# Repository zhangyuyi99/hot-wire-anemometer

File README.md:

# Hot wire anemometer

This project includes the design and implementation of a Wi-Fi enabled anemometer. The anemometer consists of a hardware portion which includes the PCB designs for the main board and logic board and a software portion which includes the firmware for operating the anemometer. The anemometer uses a hot wire method for wind speed measurement, and it includes a function to monitor battery voltage, disabling wind readings when the voltage drops below 7V until it recovers.

## Contents
1. [Hardware](#Hardware)
2. [Software](#Software)
3. [Usage](#Usage)
4. [File Structure](#File-Structure)

## Hardware
The hardware part consists of two boards: 

### Main Board
The main board uses the analog hot wire anemometer method for wind measurement. It is powered and sends signal to the logic board.

### Logic Board
The logic board contains an ESP32 processor which receives signals from the main board. It sends the data either via a serial port or Wi-Fi. It also monitors the battery voltage and provides visual feedback using LEDs.

## Software
The software part consists of firmware written for the ESP32 processor. The firmware contains routines to read data from the main board, manage Wi-Fi connectivity, monitor battery voltage, and control LED indicators.

### Python Scripts
There are two Python scripts provided for reading data:

1. `read_from_esp32.py`: Reads data over Wi-Fi. To use this, the anemometer and the computer receiving data must be on the same Wi-Fi network.

2. `read_from_esp32_serial.py`: Reads data over a serial port.

## Usage

To use this anemometer, you will need to:

1. Print the main board and logic board based on the provided PCB design files.
2. Perform necessary wirings to power up the main board and send signals to the logic board.
3. Set up Wi-Fi connectivity in the firmware.
4. Compile and upload the firmware to the logic board.
5. Calibrate the anemometer. To calibrate, place the anemometer in an environment with the same ambient temperature as the actual measurement environment. Adjust the Through Hole Potentiometer on each anemometer until the no-wind reading reaches 1000-1200. Each anemometer is paired with a green LED on the logic board. The LED lights up when the no-wind reading is in the desired range.
6. Run the provided Python scripts to receive and save the wind data. Each wind data packet is a string of numbers separated by commas. The first number is a timestamp, and the rest are the anemometer readings.

## Modes

The anemometer supports four running modes:
* READ_ANEMOMETER
* SEND_PIN_READ
* PRINT_IP
* CALIBRATE

The default mode is CALIBRATE.

## File Structure

The files in this project are organized as follows:

- plot.pptx
- logic_board/
    - Various KiCAD and SVG files for logic board design
- main_board/
    - Various KiCAD and SVG files for main board design
- firmware/
    - anemometer/
        - Python scripts to read data from the anemometer
        - ESP32 firmware files
        - Additional files for Visual Studio Code and PlatformIO

For a detailed view of the file structure, refer to the file list provided earlier.

## Note

The readings of different anemometers for the same wind strength might not be the same. However, the change in readings should accurately reflect the changes in wind conditions.

## Contribution 

The design of main board and logic board is done by Filip Ayazi. The firmware is written by Yuyi Zhang and ChatGPT, actually mostly by ChatGPT.

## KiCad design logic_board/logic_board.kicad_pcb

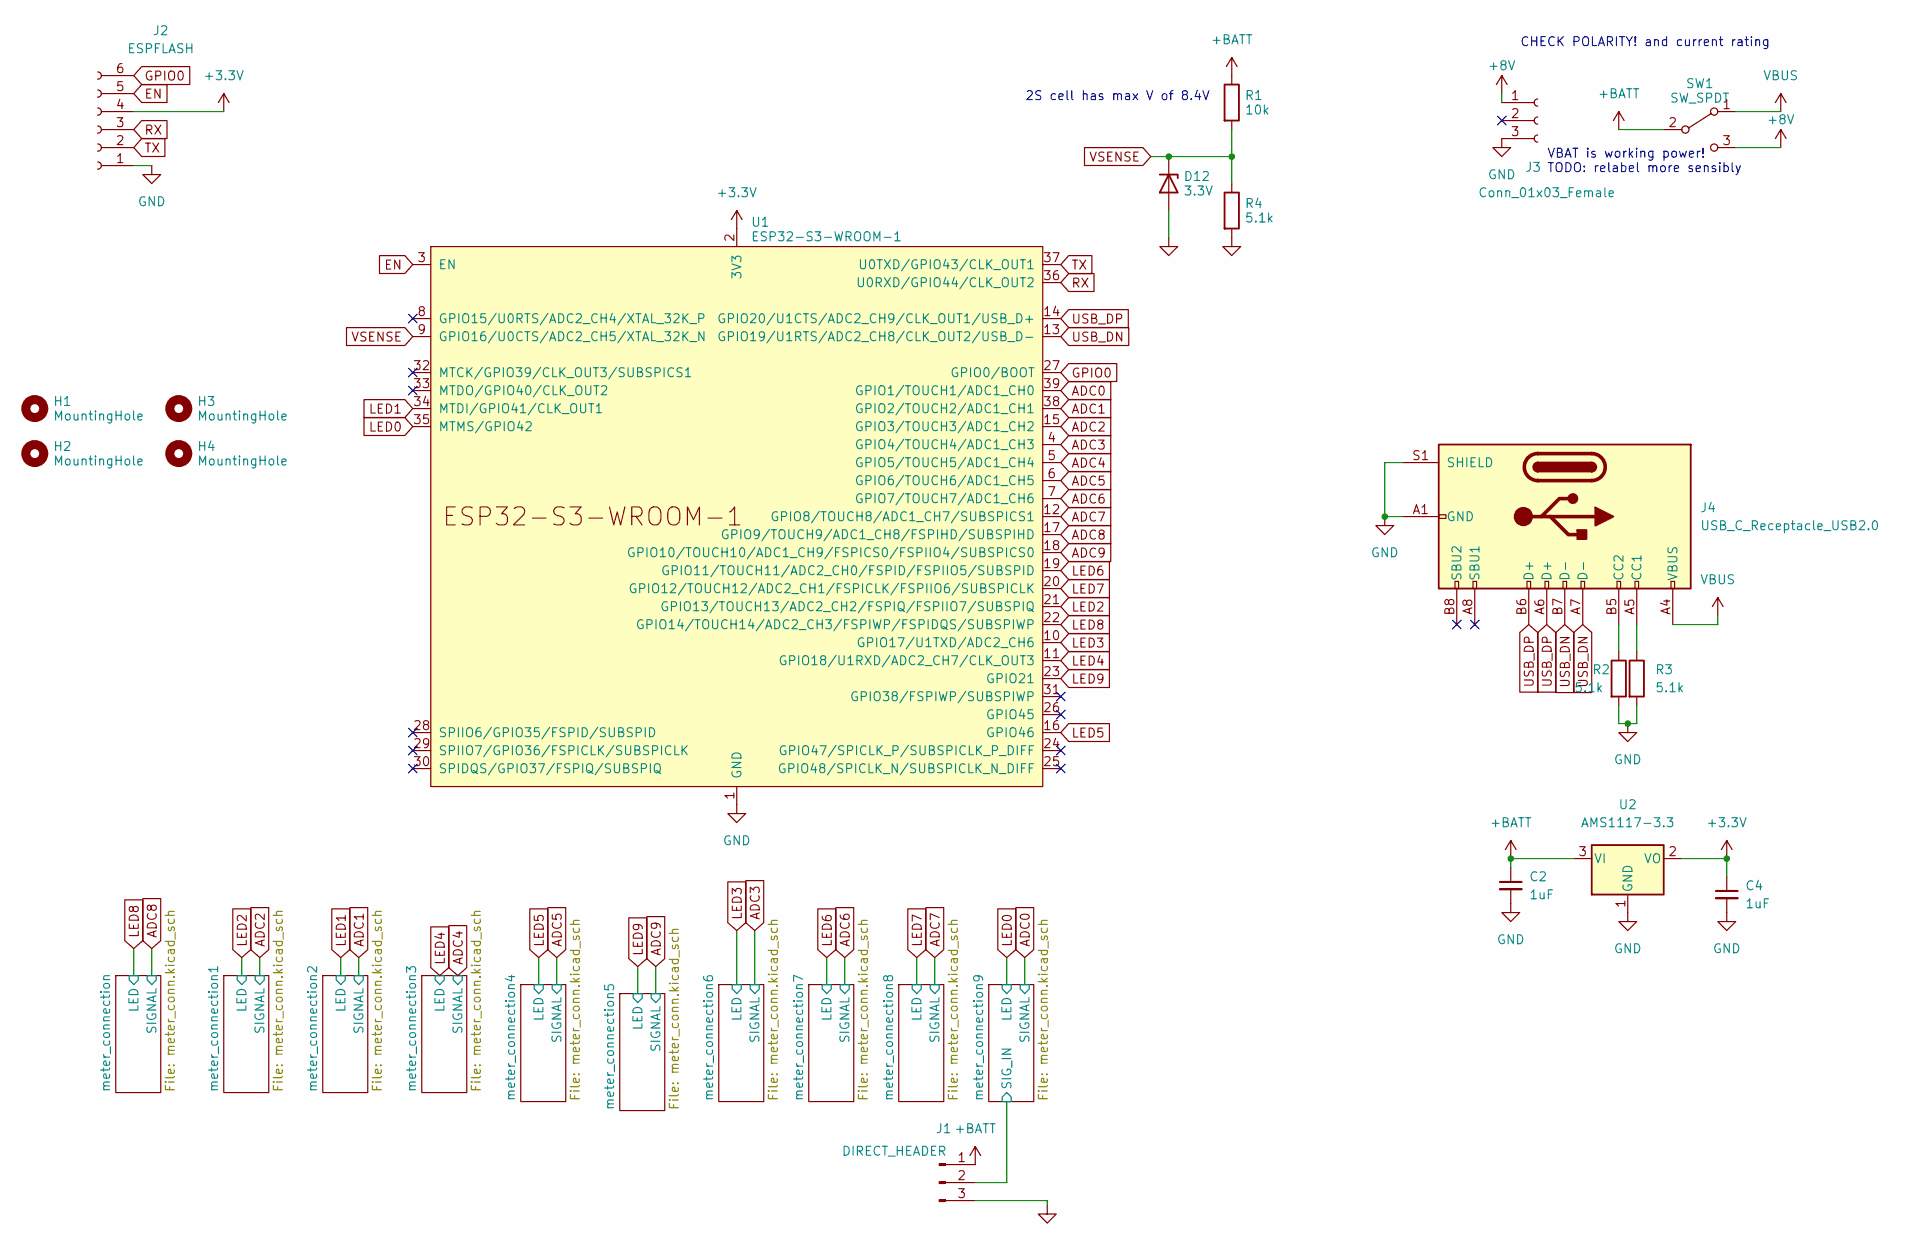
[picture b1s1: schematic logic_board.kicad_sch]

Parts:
C2, C4: 1uF; C_0402_1005Metric; JLC C83063
D12: 3.3V; D_SOD-523; JLC C2999960
H1, H2, H3, H4: MountingHole; MountingHole_3.2mm_M3
J1: DIRECT_HEADER; PinHeader_1x03_P2.54mm_Vertical; JLC C5116482
J2: ESPFLASH; PinSocket_1x06_P2.54mm_Vertical; JLC C5224026
J3: Conn_01x03_Female; JST_XH_B3B-XH-A_1x03_P2.50mm_Vertical; JLC C144394
J4: USB_C_Receptacle_USB2.0; USB_C_Receptacle_HRO_TYPE-C-31-M-12; JLC C2765186
R1: 10k; R_0402_1005Metric; JLC C407753
R2, R3, R4: 5.1k; R_0603_1608Metric; JLC C105580
SW1: SW_SPDT; switch_4.7mm; JLC C319012
U1: ESP32-S3-WROOM-1; JLC C2913197
U2: AMS1117-3.3; SOT-223-3_TabPin2; JLC C173386

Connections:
+3V3: C4.1, J2.4, U1.2 (3V3), U2.2 (VO)
+8V: J3.1, SW1.3 (C)
+BATT: C2.1, J1.1, R1.1, SW1.2 (B), U2.3 (VI); also elsewhere on the board
/meter_connection9/SIG_IN: J1.2; also elsewhere on the board
ADC0: U1.39 (GPIO1/TOUCH1/ADC1_CH0); also elsewhere on the board
ADC1: U1.38 (GPIO2/TOUCH2/ADC1_CH1); also elsewhere on the board
ADC2: U1.15 (GPIO3/TOUCH3/ADC1_CH2); also elsewhere on the board
ADC3: U1.4 (GPIO4/TOUCH4/ADC1_CH3); also elsewhere on the board
ADC4: U1.5 (GPIO5/TOUCH5/ADC1_CH4); also elsewhere on the board
ADC5: U1.6 (GPIO6/TOUCH6/ADC1_CH5); also elsewhere on the board
ADC6: U1.7 (GPIO7/TOUCH7/ADC1_CH6); also elsewhere on the board
ADC7: U1.12 (GPIO8/TOUCH8/ADC1_CH7/SUBSPICS1); also elsewhere on the board
ADC8: U1.17 (GPIO9/TOUCH9/ADC1_CH8/FSPIHD/SUBSPIHD); also elsewhere on the board
ADC9: U1.18 (GPIO10/TOUCH10/ADC1_CH9/FSPICS0/FSPIIO4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); also elsewhere on the board
EN: J2.5, U1.3 (EN)
GND: C2.2, C4.2, D12.2 (A), J1.3, J2.1, J3.3, J4.A1 (GND), J4.A12 (GND), J4.B1 (GND), J4.B12 (GND), J4.S1 (SHIELD), R2.2, R3.2, R4.2, U1.1 (GND), U1.40 (GND), U1.41 (GND), U2.1 (GND); also elsewhere on the board
GPIO0: J2.6, U1.27 (GPIO0/BOOT)
LED0: U1.35 (MTMS/GPIO42); also elsewhere on the board
LED1: U1.34 (MTDI/GPIO41/CLK_OUT1); also elsewhere on the board
LED2: U1.21 (GPIO13/TOUCH13/ADC2_CH2/FSPIQ/FSPIIO7/S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); also elsewhere on the board
LED3: U1.10 (GPIO17/U1TXD/ADC2_CH6); also elsewhere on the board
LED4: U1.11 (GPIO18/U1RXD/ADC2_CH7/CLK_OUT3); also elsewhere on the board
LED5: U1.16 (GPIO46); also elsewhere on the board
LED6: U1.19 (GPIO11/TOUCH11/ADC2_CH0/FSPID/FSPIIO5/S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); also elsewhere on the board
LED7: U1.20 (GPIO12/TOUCH12/ADC2_CH1/FSPICLK/FSPIIO6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); also elsewhere on the board
LED8: U1.22 (GPIO14/TOUCH14/ADC2_CH3/FSPIWP/FSPIDQS/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); also elsewhere on the board
LED9: U1.23 (GPIO21); also elsewhere on the board
unnamed: J4.A5 (CC1), R3.1
unnamed: J4.B5 (CC2), R2.1
RX: J2.3, U1.36 (U0RXD/GPIO44/CLK_OUT2)
TX: J2.2, U1.37 (U0TXD/GPIO43/CLK_OUT1)
USB_DN: J4.A7 (D-), J4.B7 (D-), U1.13 (GPIO19/U1RTS/ADC2_CH8/CLK_OUT2/USB_D-)
USB_DP: J4.A6 (D+), J4.B6 (D+), U1.14 (GPIO20/U1CTS/ADC2_CH9/CLK_OUT1/USB_D+)
VBUS: J4.A4 (VBUS), J4.A9 (VBUS), J4.B4 (VBUS), J4.B9 (VBUS), SW1.1 (A)

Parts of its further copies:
D1, D13, D14, D15, D16, D17, D18, D19, D20, D21: 3.3V; D_SOD-523; JLC C2999960

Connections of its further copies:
GND: D1.2 (A), D13.2 (A), D14.2 (A), D15.2 (A), D16.2 (A), D17.2 (A), D18.2 (A), D19.2 (A), D20.2 (A), D21.2 (A); also elsewhere on the board
unnamed 46: D13.1 (K); also elsewhere on the board
unnamed 47: D14.1 (K); also elsewhere on the board
unnamed 48: D15.1 (K); also elsewhere on the board
unnamed 49: D16.1 (K); also elsewhere on the board
unnamed 50: D17.1 (K); also elsewhere on the board
unnamed 51: D18.1 (K); also elsewhere on the board
unnamed 52: D19.1 (K); also elsewhere on the board
unnamed 53: D20.1 (K); also elsewhere on the board
unnamed 54: D21.1 (K); also elsewhere on the board

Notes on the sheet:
2S cell has max V of 8.4V
VBAT is working power! TODO: relabel more sensibly
CHECK POLARITY! and current rating

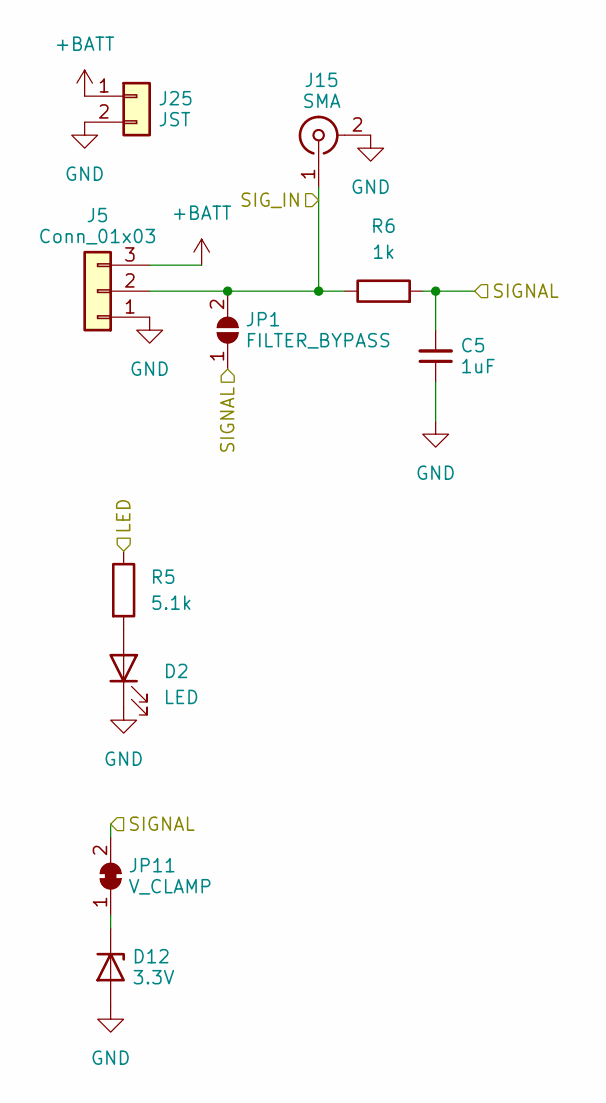
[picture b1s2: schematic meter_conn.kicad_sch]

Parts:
C5: 1uF; C_0402_1005Metric; JLC C83063
D2: LED; LED_0805_2012Metric; JLC C2297
D12: 3.3V; D_SOD-523; JLC C2999960
J5: Conn_01x03; JST_PH_B3B-PH-K_1x03_P2.00mm_Vertical; JLC C131339
J15: SMA; SMA_Amphenol_901-143_Horizontal; JLC C411575
J25: JST; JST_PH_B2B-PH-K_1x02_P2.00mm_Vertical; JLC C131337
JP1: FILTER_BYPASS; SolderJumper-2_P1.3mm_Open_RoundedPad1.0x1.5mm
JP11: V_CLAMP; SolderJumper-2_P1.3mm_Bridged2Bar_RoundedPad1.0x1.5mm
R5: 5.1k; R_0603_1608Metric; JLC C105580
R6: 1k; R_0402_1005Metric; JLC C208774

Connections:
+BATT: J5.3, J25.1; also elsewhere on the board
/meter_connection/SIG_IN: J5.2, J15.1 (In), JP1.2 (B), R6.1
ADC8: C5.2, JP1.1 (A), JP11.2 (B), R6.2; also elsewhere on the board
GND: C5.1, D2.1 (K), D12.2 (A), J5.1, J15.2 (Ext), J25.2; also elsewhere on the board
LED8: R5.1; also elsewhere on the board
unnamed: D2.2 (A), R5.2

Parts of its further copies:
C6, C7, C8, C9, C10, C11, C12, C13, C14: 1uF; C_0402_1005Metric; JLC C83063
D3, D4, D5, D6, D7, D8, D9, D10, D11: LED; LED_0805_2012Metric; JLC C2297
D13, D14, D15, D16, D17, D18, D19, D20, D21: 3.3V; D_SOD-523; JLC C2999960
J6, J7, J8, J9, J10, J11, J12, J13, J14: Conn_01x03; JST_PH_B3B-PH-K_1x03_P2.00mm_Vertical; JLC C131339
J16, J17, J18, J19, J20, J21, J22, J23, J24: SMA; SMA_Amphenol_901-143_Horizontal; JLC C411575
J26, J27, J28, J29, J30, J31, J32, J33, J34: JST; JST_PH_B2B-PH-K_1x02_P2.00mm_Vertical; JLC C131337
JP2, JP3, JP4, JP5, JP6, JP7, JP8, JP9, JP10: FILTER_BYPASS; SolderJumper-2_P1.3mm_Open_RoundedPad1.0x1.5mm
JP12, JP13, JP14, JP15, JP16, JP17, JP18, JP19, JP20: V_CLAMP; SolderJumper-2_P1.3mm_Bridged2Bar_RoundedPad1.0x1.5mm
R7, R9, R11, R13, R15, R17, R19, R21, R23: 5.1k; R_0603_1608Metric; JLC C105580
R8, R10, R12, R14, R16, R18, R20, R22, R24: 1k; R_0402_1005Metric; JLC C208774

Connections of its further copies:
+BATT: J6.3, J7.3, J8.3, J9.3, J10.3, J11.3, J12.3, J13.3, J14.3, J26.1, J27.1, J28.1, J29.1, J30.1, J31.1, J32.1, J33.1, J34.1; also elsewhere on the board
/meter_connection1/SIG_IN: J6.2, J16.1 (In), JP2.2 (B), R8.1
/meter_connection2/SIG_IN: J7.2, J17.1 (In), JP3.2 (B), R10.1
/meter_connection3/SIG_IN: J8.2, J18.1 (In), JP4.2 (B), R12.1
/meter_connection4/SIG_IN: J9.2, J19.1 (In), JP5.2 (B), R14.1
/meter_connection5/SIG_IN: J10.2, J20.1 (In), JP6.2 (B), R16.1
/meter_connection6/SIG_IN: J11.2, J21.1 (In), JP7.2 (B), R18.1
/meter_connection7/SIG_IN: J12.2, J22.1 (In), JP8.2 (B), R20.1
/meter_connection8/SIG_IN: J13.2, J23.1 (In), JP9.2 (B), R22.1
/meter_connection9/SIG_IN: J14.2, J24.1 (In), JP10.2 (B), R24.1; also elsewhere on the board
ADC0: C14.2, JP10.1 (A), JP20.2 (B), R24.2; also elsewhere on the board
ADC1: C7.2, JP3.1 (A), JP13.2 (B), R10.2; also elsewhere on the board
ADC2: C6.2, JP2.1 (A), JP12.2 (B), R8.2; also elsewhere on the board
ADC3: C11.2, JP7.1 (A), JP17.2 (B), R18.2; also elsewhere on the board
ADC4: C8.2, JP4.1 (A), JP14.2 (B), R12.2; also elsewhere on the board
ADC5: C9.2, JP5.1 (A), JP15.2 (B), R14.2; also elsewhere on the board
ADC6: C12.2, JP8.1 (A), JP18.2 (B), R20.2; also elsewhere on the board
ADC7: C13.2, JP9.1 (A), JP19.2 (B), R22.2; also elsewhere on the board
ADC9: C10.2, JP6.1 (A), JP16.2 (B), R16.2; also elsewhere on the board
GND: C6.1, C7.1, C8.1, C9.1, C10.1, C11.1, C12.1, C13.1, C14.1, D3.1 (K), D4.1 (K), D5.1 (K), D6.1 (K), D7.1 (K), D8.1 (K), D9.1 (K), D10.1 (K), D11.1 (K), D13.2 (A), D14.2 (A), D15.2 (A), D16.2 (A), D17.2 (A), D18.2 (A), D19.2 (A), D20.2 (A), D21.2 (A), J6.1, J7.1, J8.1, J9.1, J10.1, J11.1, J12.1, J13.1, J14.1, J16.2 (Ext), J17.2 (Ext), J18.2 (Ext), J19.2 (Ext), J20.2 (Ext), J21.2 (Ext), J22.2 (Ext), J23.2 (Ext), J24.2 (Ext), J26.2, J27.2, J28.2, J29.2, J30.2, J31.2, J32.2, J33.2, J34.2; also elsewhere on the board
LED0: R23.1; also elsewhere on the board
LED1: R9.1; also elsewhere on the board
LED2: R7.1; also elsewhere on the board
LED3: R17.1; also elsewhere on the board
LED4: R11.1; also elsewhere on the board
LED5: R13.1; also elsewhere on the board
LED6: R19.1; also elsewhere on the board
LED7: R21.1; also elsewhere on the board
LED9: R15.1; also elsewhere on the board
unnamed: D3.2 (A), R7.2
unnamed: D4.2 (A), R9.2
unnamed: D5.2 (A), R11.2
unnamed: D6.2 (A), R13.2
unnamed: D7.2 (A), R15.2
unnamed: D8.2 (A), R17.2
unnamed: D9.2 (A), R19.2
unnamed: D10.2 (A), R21.2
unnamed: D11.2 (A), R23.2
unnamed: D13.1 (K), JP12.1 (A)
unnamed: D14.1 (K), JP13.1 (A)
unnamed: D15.1 (K), JP14.1 (A)
unnamed: D16.1 (K), JP15.1 (A)
unnamed: D17.1 (K), JP16.1 (A)
unnamed: D18.1 (K), JP17.1 (A)
unnamed: D19.1 (K), JP18.1 (A)
unnamed: D20.1 (K), JP19.1 (A)
unnamed: D21.1 (K), JP20.1 (A)

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
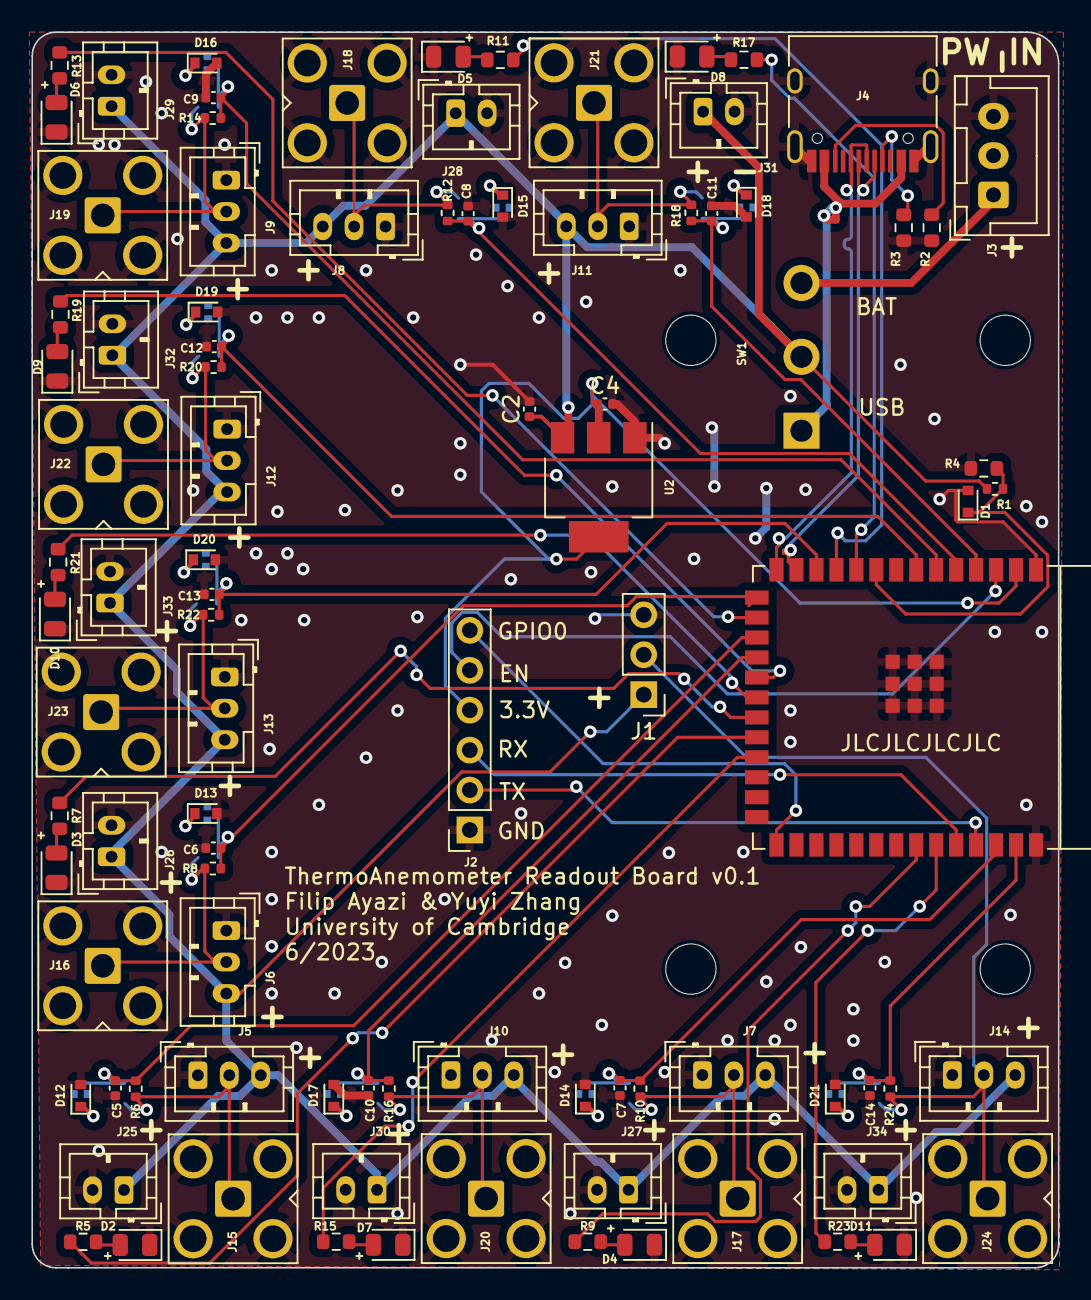
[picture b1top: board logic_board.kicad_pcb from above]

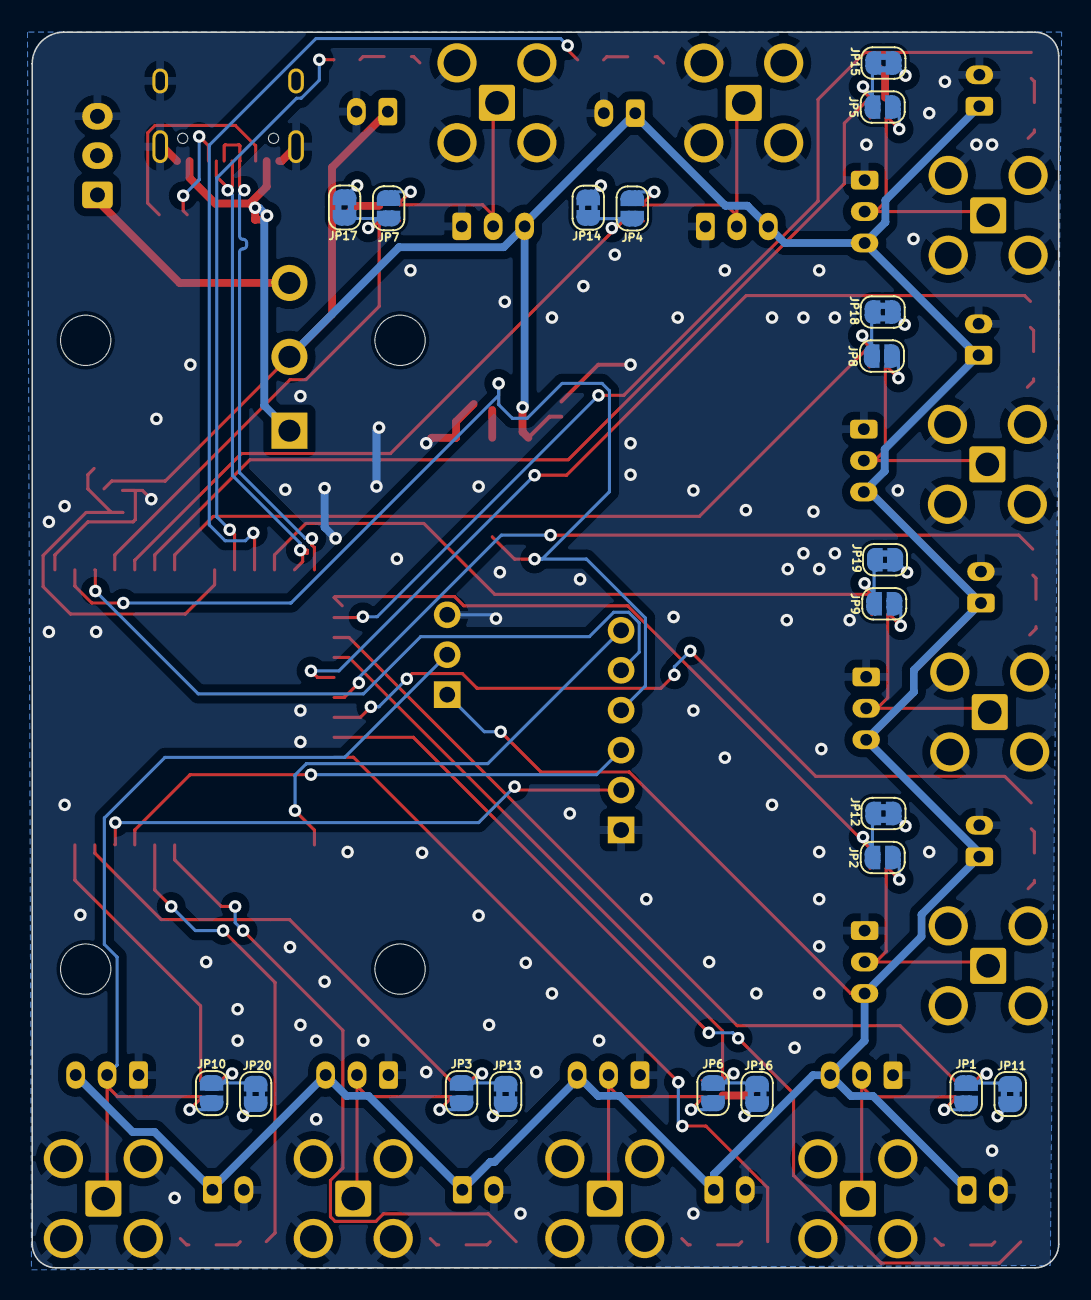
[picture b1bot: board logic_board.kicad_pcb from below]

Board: 2 copper layers, 65.3 x 78.6 mm, 118 parts (20 on the bottom side), 64 nets.

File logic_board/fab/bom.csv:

Comment,Designator,Footprint,LCSC
DIRECT_HEADER,J1,Connector_PinHeader_2.54mm:PinHeader_1x03_P2.54mm_Vertical,C5116482
USB_C_Receptacle_USB2.0,J4,Connector_USB:USB_C_Receptacle_HRO_TYPE-C-31-M-12,C2765186
3.3V,"D1,D12,D13,D14,D15,D16,D17,D18,D19,D20,D21",Diode_SMD:D_SOD-523,C2999960
1uF,"C2,C4,C5,C6,C7,C8,C9,C10,C11,C12,C13,C14",Capacitor_SMD:C_0402_1005Metric,C301999
10k,R1,Resistor_SMD:R_0402_1005Metric,C407753
Conn_01x03_Female,J3,Connector_JST:JST_XH_B3B-XH-A_1x03_P2.50mm_Vertical,C144394
5.1k,"R2,R3,R4,R5,R7,R9,R11,R13,R15,R17,R19,R21,R23",Resistor_SMD:R_0603_1608Metric,C25197
SW_SPDT,SW1,library:switch_4.7mm,C319012
ESP32-S3-WROOM-1,U1,PCM_Espressif:ESP32-S3-WROOM-1,C2913197
AMS1117-3.3,U2,Package_TO_SOT_SMD:SOT-223-3_TabPin2,C173386
ESPFLASH,J2,Connector_PinSocket_2.54mm:PinSocket_1x06_P2.54mm_Vertical,C5224026
JST,"J25,J26,J27,J28,J29,J30,J31,J32,J33,J34",Connector_JST:JST_PH_B2B-PH-K_1x02_P2.00mm_Vertical,C131337
SMA,"J15,J16,J17,J18,J19,J20,J21,J22,J23,J24",library:SMA_Amphenol_901-143_Horizontal,C411575
1k,"R6,R8,R10,R12,R14,R16,R18,R20,R22,R24",Resistor_SMD:R_0402_1005Metric,C208774
LED,"D2,D3,D4,D5,D6,D7,D8,D9,D10,D11",LED_SMD:LED_0805_2012Metric,C2297
Conn_01x03,"J5,J6,J7,J8,J9,J10,J11,J12,J13,J14",Connector_JST:JST_PH_B3B-PH-K_1x03_P2.00mm_Vertical,C131339

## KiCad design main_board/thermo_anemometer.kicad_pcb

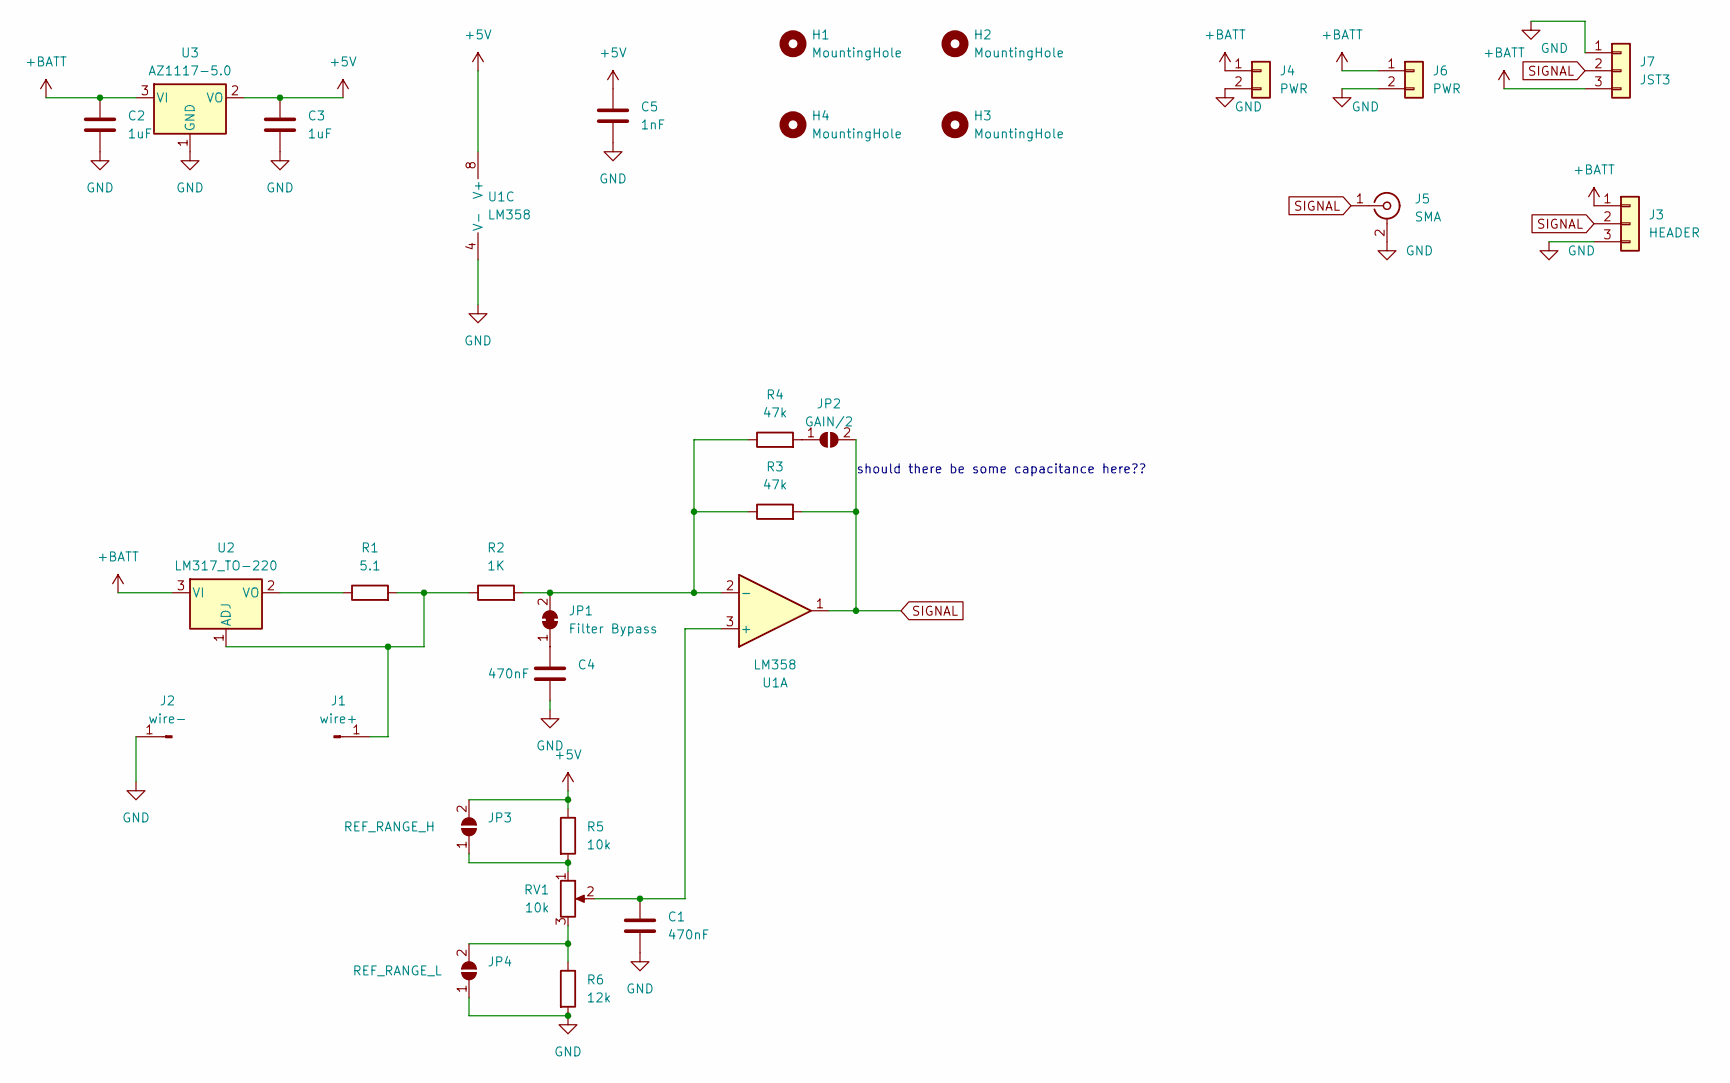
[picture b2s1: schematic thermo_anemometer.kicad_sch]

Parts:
C1, C4: 470nF; C_0402_1005Metric; JLC C426055
C2, C3: 1uF; C_0603_1608Metric; JLC C106848
C5: 1nF; C_0402_1005Metric; JLC C93920
H1, H2, H3, H4: MountingHole; MountingHole_3.2mm_M3
J1: wire+; m2.5_pad
J2: wire-; m2.5_pad
J3: HEADER; PinSocket_1x03_P2.54mm_Vertical; JLC C358717
J4: PWR; SolderWire-0.5sqmm_1x02_P4.6mm_D0.9mm_OD2.1mm
J5: SMA; SMA_Amphenol_901-143_Horizontal; JLC C411575
J6: PWR; JST_PH_B2B-PH-K_1x02_P2.00mm_Vertical; JLC C131337
J7: JST3; JST_PH_B3B-PH-K_1x03_P2.00mm_Vertical; JLC C131339
JP1: Filter Bypass; SolderJumper-2_P1.3mm_Bridged_RoundedPad1.0x1.5mm
JP2: GAIN/2; SolderJumper-2_P1.3mm_Open_RoundedPad1.0x1.5mm
JP3: REF_RANGE_H; SolderJumper-2_P1.3mm_Open_RoundedPad1.0x1.5mm
JP4: REF_RANGE_L; SolderJumper-2_P1.3mm_Open_RoundedPad1.0x1.5mm
R1: 5.1; R_2512_6332Metric; JLC C105134
R2: 1K; R_0603_1608Metric; JLC C103198
R3, R4: 47k; R_0603_1608Metric; JLC C340515
R5: 10k; R_0603_1608Metric; JLC C160601
R6: 12k; R_0603_1608Metric; JLC C2984432
RV1: 10k; Potentiometer_Bourns_3386P_Vertical; JLC C118953
U1: LM358; SOP-8_3.76x4.96mm_P1.27mm; JLC C5252902
U2: LM317_TO-220; SOT-223; JLC C347367
U3: AZ1117-5.0; SOT-89-3; JLC C24248

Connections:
+5V: C3.1, C5.1, JP3.2 (B), R5.1, U1.8 (V+), U3.2 (VO)
+BATT: C2.1, J3.1, J4.1, J6.1, J7.3, U2.3 (VI), U3.3 (VI)
GND: C1.2, C2.2, C3.2, C4.2, C5.2, J2.1, J3.3, J4.2, J5.2 (Ext), J6.2, J7.1, JP4.1 (A), R6.2, U1.4 (V-), U3.1 (GND)
unnamed: J1.1, R1.2, R2.1, U2.1 (ADJ)
unnamed: C4.1, JP1.1 (A)
unnamed: JP1.2 (B), R2.2, R3.1, R4.1, U1.2 (-)
unnamed: JP2.1 (A), R4.2
unnamed: JP3.1 (A), R5.2, RV1.1
unnamed: JP4.2 (B), R6.1, RV1.3
unnamed: C1.1, RV1.2, U1.3 (+)
unnamed: R1.1, U2.2 (VO)
SIGNAL: J3.2, J5.1 (In), J7.2, JP2.2 (B), R3.2, U1.1

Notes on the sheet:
should there be some capacitance here??

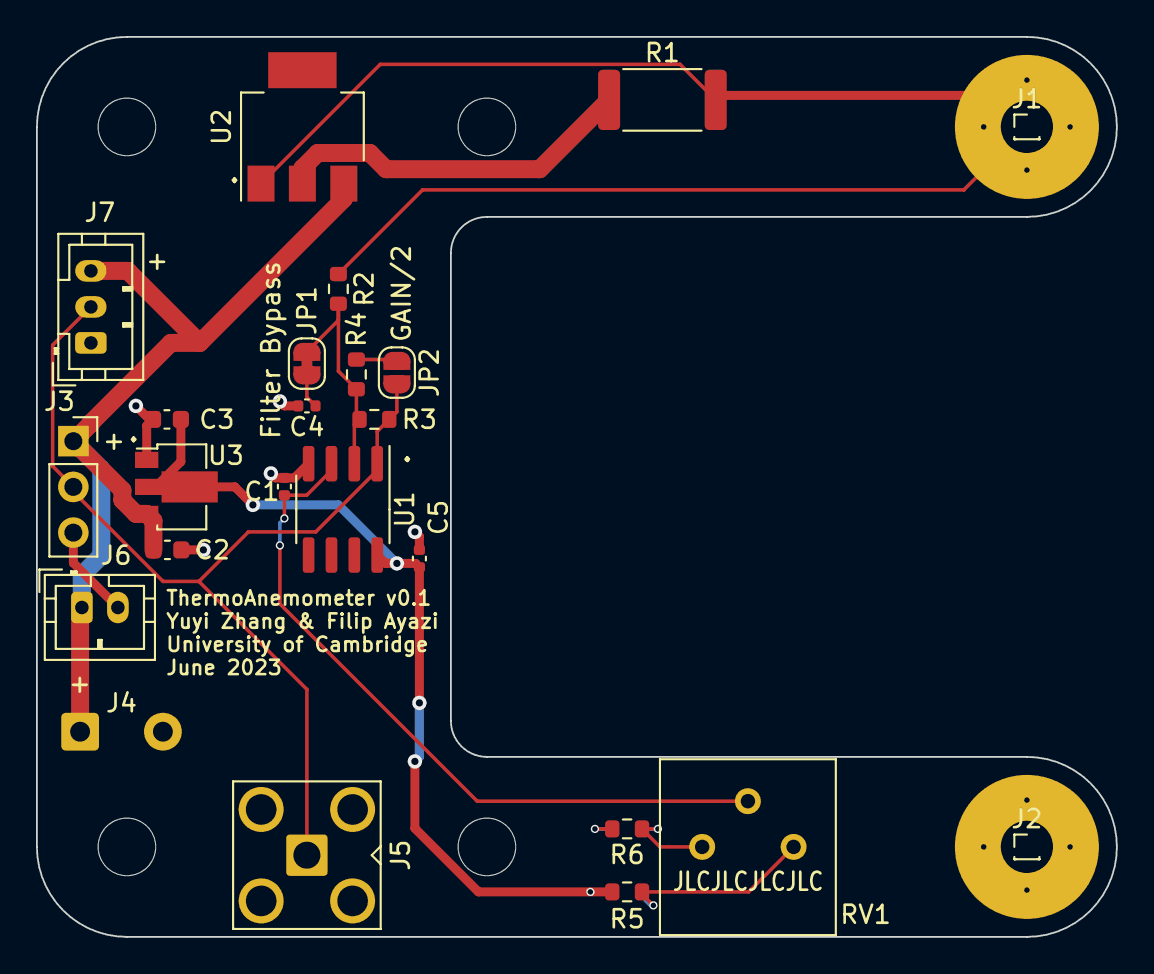
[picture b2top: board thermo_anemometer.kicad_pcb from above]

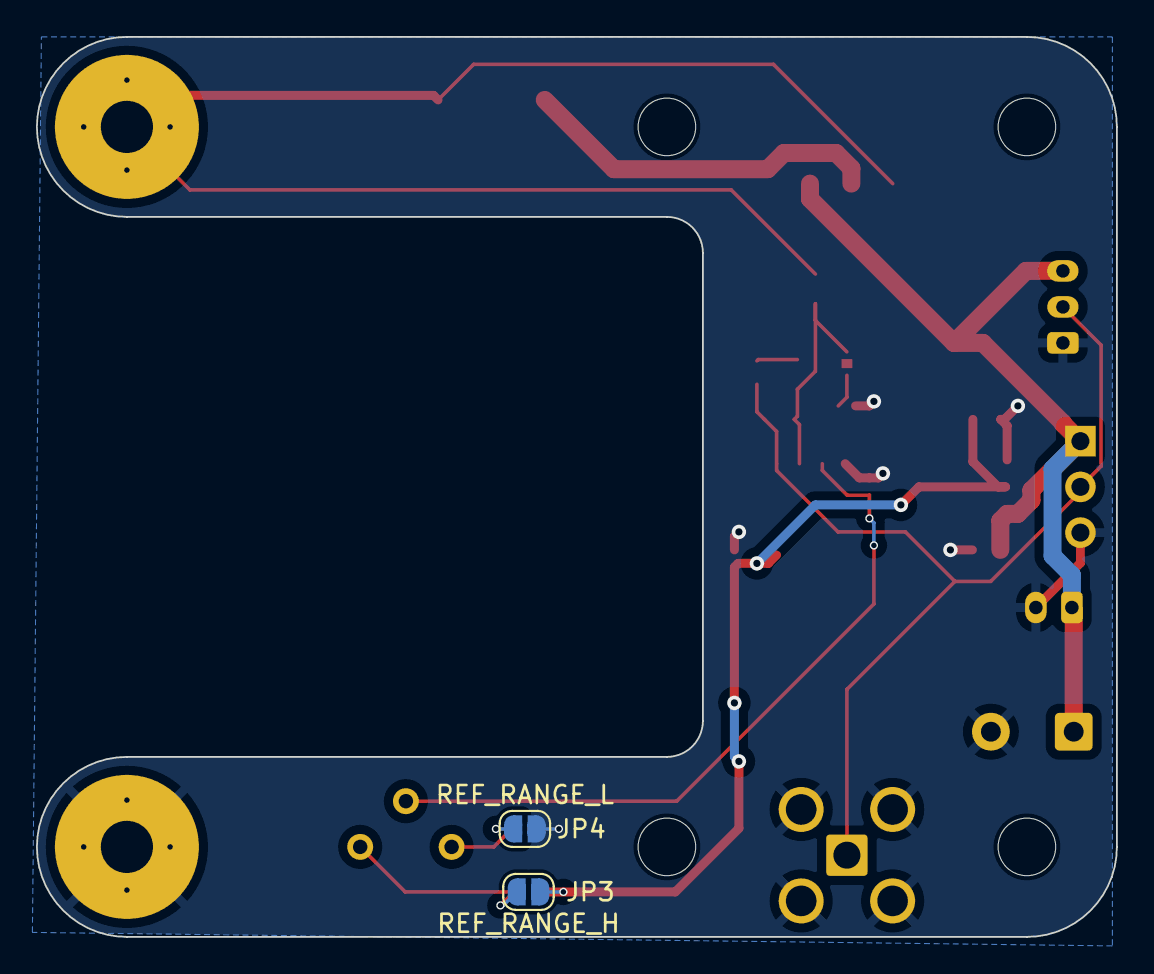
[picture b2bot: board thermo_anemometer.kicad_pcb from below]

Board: 2 copper layers, 60.0 x 50.0 mm, 30 parts (2 on the bottom side), 12 nets.

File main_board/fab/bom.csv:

Comment,Designator,Footprint,LCSC
HEADER,J3,Connector_PinSocket_2.54mm:PinSocket_1x03_P2.54mm_Vertical,C358717
1nF,C5,Capacitor_SMD:C_0402_1005Metric,C93920
PWR,J6,Connector_JST:JST_PH_B2B-PH-K_1x02_P2.00mm_Vertical,C131337
470nF,"C1,C4",Capacitor_SMD:C_0402_1005Metric,C426055
AZ1117-5.0,U3,Package_TO_SOT_SMD:SOT-89-3,C24248
wire+,J1,Library:m2.5_pad,
wire-,J2,Library:m2.5_pad,
10k,R5,Resistor_SMD:R_0603_1608Metric,C160601
47k,"R3,R4",Resistor_SMD:R_0603_1608Metric,C340515
JST3,J7,Connector_JST:JST_PH_B3B-PH-K_1x03_P2.00mm_Vertical,C131339
1K,R2,Resistor_SMD:R_0603_1608Metric,C103198
SMA,J5,Connector_Coaxial:SMA_Amphenol_901-143_Horizontal,C411575
5.1,R1,Resistor_SMD:R_2512_6332Metric,C105134
1uF,"C2,C3",Capacitor_SMD:C_0603_1608Metric,C106848
12k,R6,Resistor_SMD:R_0603_1608Metric,C2984432
LM317_TO-220,U2,Package_TO_SOT_SMD:SOT-223,C347367
10k,RV1,Potentiometer_THT:Potentiometer_Bourns_3386P_Vertical,C118953
LM358,U1,Package_SO:SOP-8_3.76x4.96mm_P1.27mm,C5252902
